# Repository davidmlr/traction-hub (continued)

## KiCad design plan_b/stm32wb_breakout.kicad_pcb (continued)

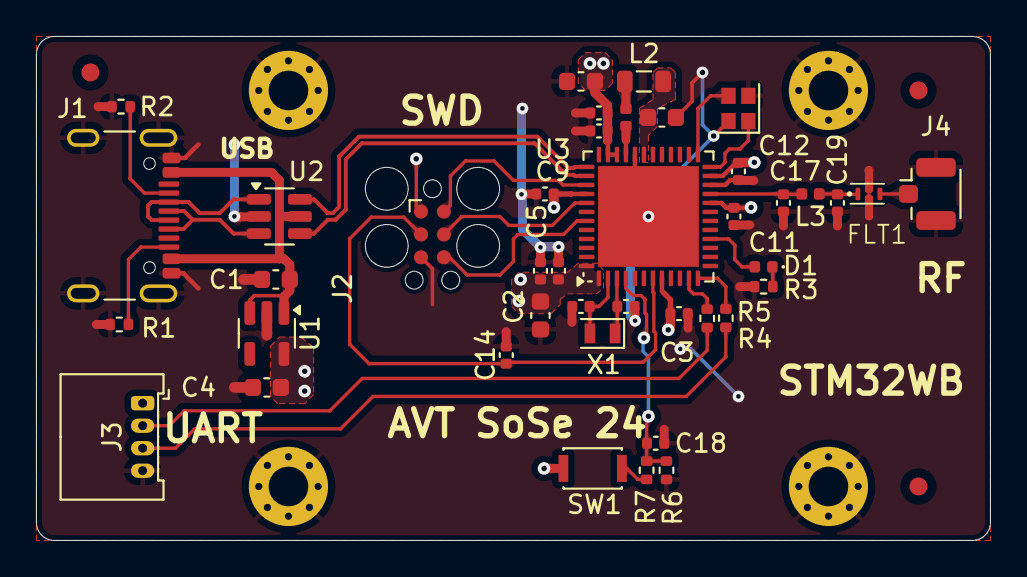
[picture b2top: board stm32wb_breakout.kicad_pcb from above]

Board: 2 copper layers, 53.0 x 28.0 mm, 48 parts (0 on the bottom side), 31 nets.

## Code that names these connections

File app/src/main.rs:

#![no_std]
#![no_main]

mod fmt;

mod current_sense;
mod stream;
mod usb_telem;

#[cfg(feature = "defmt")]
use defmt_rtt as _;

use core::sync::atomic::{AtomicU8, Ordering};

use embassy_executor::Spawner;
use embassy_stm32::{
    adc::{Adc, AdcChannel, AdcConfig, InjectedTrigger, Resolution, SampleTime},
    bind_interrupts,
    gpio::{Level, Output, OutputType, Speed},
    pac,
    peripherals::ADC1,
    time::khz,
    timer::{
        complementary_pwm::{ComplementaryPwm, ComplementaryPwmPin, Mms2},
        simple_pwm::PwmPin,
        Channel,
    },
};
use embassy_time::Timer;
use fmt::info;

pub struct Tim1Trgo2;
impl InjectedTrigger<ADC1> for Tim1Trgo2 {
    fn signal(&self) -> u8 {
        8
    }
}

/// Current commutation step (1..=6), 0 while stopped.
pub static STEP: AtomicU8 = AtomicU8::new(0);

bind_interrupts!( struct Irqs {
    ADC1_2 => current_sense::CurrentSenseIrq;
    USB_LP => embassy_stm32::usb::InterruptHandler<embassy_stm32::peripherals::USB>;
});

#[embassy_executor::main]
async fn main(spawner: Spawner) {
    // Stop TIM1 and disable outputs when core is halted by debugger
    pac::DBGMCU.apb2fzr().modify(|w| w.set_tim1(true));
    let mut config = embassy_stm32::Config::default();
    {
        use embassy_stm32::rcc::*;
        // Not in use for now
        // config.rcc.hse = Some(Hse {
        //     freq: Hertz(24_000_000),
        //     mode: HseMode::Oscillator,
        // });
        config.rcc.pll = Some(Pll {
            source: PllSource::HSI,
            prediv: PllPreDiv::DIV4, // 16 MHz / 4 = 4 MHz VCO input
            mul: PllMul::MUL40,      // 4 MHz * 40  = 160 MHz VCO
            divp: None,
            divq: None,
            divr: Some(PllRDiv::DIV2), // 160 MHz / 2 = 80 MHz SYSCLK
        });
        config.rcc.sys = Sysclk::PLL1_R;
        config.rcc.mux.adc12sel = mux::Adcsel::SYS;
        config.rcc.hsi48 = Some(Default::default());
        config.rcc.mux.clk48sel = mux::Clk48sel::HSI48;
    }
    let p = embassy_stm32::init(config);

    //USB
    usb_telem::init(spawner, p.USB, Irqs, p.PA12, p.PA11);

    //ADC
    let mut adc_config = AdcConfig::default();
    adc_config.resolution = Some(Resolution::BITS12);
    let mut adc = Adc::new(p.ADC1, adc_config);
    let mut vrefint = adc.enable_vrefint();
    let vrefint_raw = adc.blocking_read(&mut vrefint, SampleTime::CYCLES640_5);

    // Must stay alive: dropping it stops the ADC
    let _inj = adc.setup_injected_conversions(
        [
            (p.PB1.degrade_adc(), SampleTime::CYCLES12_5),
            (p.PB0.degrade_adc(), SampleTime::CYCLES12_5),
        ],
        Tim1Trgo2,
        embassy_stm32::adc::Exten::RISING_EDGE,
        true,
    );

    // MOTOR
    let mut en = Output::new(p.PA15, Level::Low, Speed::Low);

    let ch1 = PwmPin::new(p.PA8, OutputType::PushPull);
    let ch1n = ComplementaryPwmPin::new(p.PB13, OutputType::PushPull);
    let ch2 = PwmPin::new(p.PA9, OutputType::PushPull);
    let ch2n = ComplementaryPwmPin::new(p.PB14, OutputType::PushPull);
    let ch3 = PwmPin::new(p.PA10, OutputType::PushPull);
    let ch3n = ComplementaryPwmPin::new(p.PB15, OutputType::PushPull);

    let mut pwm = ComplementaryPwm::new(
        p.TIM1,
        Some(ch1),
        Some(ch1n),
        Some(ch2),
        Some(ch2n),
        Some(ch3),
        Some(ch3n),
        None,
        None,
        khz(20),
        embassy_stm32::timer::low_level::CountingMode::CenterAlignedUpInterrupts,
    );

    let max = pwm.get_max_duty();
    pwm.set_dead_time((max / 1024) as u16);
    pwm.set_duty(Channel::Ch4, max - 1);
    pwm.set_mms2(Mms2::COMPARE_OC4);

    let duty = max / 10;

    pwm.disable(Channel::Ch1);
    pwm.disable(Channel::Ch2);
    pwm.disable(Channel::Ch3);

    Timer::after_millis(100).await;

    current_sense::enable(Irqs);

    en.set_high();
    Timer::after_millis(10).await;

    // Power stage still off, so this is the zero-current offset
    let cal = current_sense::calibrate(vrefint_raw, 256).await;
    usb_telem::set_calibration(cal);
    let (bias_a_mv, bias_c_mv) = cal.bias_mv();
    info!("bias_a: {} mV | bias_c: {} mV", bias_a_mv, bias_c_mv);

    let mut step: u8 = 1;
    let mut period_us: u64 = 6000;
    let mut log_div: u32 = 0;

    loop {
        //(Quelle = +V/PWM, Senke = GND/statisch, floatend)   A=Ch1  B=Ch2  C=Ch3
        let (src, sink, flt) = match step {
            1 => (Channel::Ch1, Channel::Ch3, Channel::Ch2), // A→C
            2 => (Channel::Ch1, Channel::Ch2, Channel::Ch3), // A→B
            3 => (Channel::Ch3, Channel::Ch2, Channel::Ch1), // C→B
            4 => (Channel::Ch3, Channel::Ch1, Channel::Ch2), // C→A
            5 => (Channel::Ch2, Channel::Ch1, Channel::Ch3), // B→A
            _ => (Channel::Ch2, Channel::Ch3, Channel::Ch1), // B→C
        };

        pwm.disable(flt); // beide FETs aus → Phase floatet
        pwm.set_duty(sink, 0); // Duty 0 → Low-Side dauerhaft an
        pwm.enable(sink);
        pwm.set_duty(src, duty); // High-Side choppt, Low-Side = Komplement
        pwm.enable(src);
        STEP.store(step, Ordering::Relaxed);

        log_div += 1;
        if log_div >= 50 {
            log_div = 0;
            let (raw_a, raw_c) = current_sense::latest();
            let (i_a, i_c) = cal.to_amps(raw_a, raw_c);
            info!("step {} | i_a: {} A | i_c: {} A", step, i_a, i_c);
        }

        Timer::after_micros(period_us).await;

        step = if step >= 6 { 1 } else { step + 1 };
        if period_us > 1000 {
            period_us -= 5;
        }
    }
}

#[panic_handler]
fn panic(info: &core::panic::PanicInfo) -> ! {
    // Power Stage off
    pac::TIM1.bdtr().modify(|w| w.set_moe(false));
    // Disable gate driver (drive PA15 low)
    pac::GPIOA.bsrr().write(|w| w.set_br(15, true));
    #[cfg(feature = "defmt")]
    defmt::error!("{}", defmt::Display2Format(info));
    cortex_m::asm::udf()
}

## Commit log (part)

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2024-06-12 add kicad project
2024-06-13 pcb: add regulators and stm32
2024-07-09 pcb: wip
2024-07-10 pcb: first version schematic
2024-07-11 pcb: complete bom and first layout
2024-07-11 pcb: plan_b ready for production
2024-07-11 pcb: outlines ready
2024-07-11 add readme png
2024-07-23 pcb: layout wip
2024-07-26 pcb: layout power
2024-07-28 pcb: layout gate driver
2024-07-29 pcb: v1.0 layout finsihed
2024-07-29 pcb: remove kicad backups
2024-08-17 add rust embassy project
2024-08-18 read in dc-link voltage
2024-09-06 code: add drv interfaces + simple switching test
2024-09-06 code: remove dead code
2025-04-06 code: bldc running open loop
2025-04-06 code: usb serial test
2025-04-06 add kicad .lck file to gitignore
2025-08-30 code: start from new
2025-08-30 code: add hse config
2025-08-30 code: basic starting point for task orchestration
2025-08-30 code: measure actual voltage
2025-08-30 code: add usb task
2026-02-03 some work on usb or something like that
2026-05-06 fix bugs
2026-05-06 chore: init empty embassy project
2026-05-15 feat: add simple usb logging
2026-06-25 feat: add gui app
2026-06-29 feat: add open loop pwm control
2026-06-30 feat(app): add usb cdc logging
